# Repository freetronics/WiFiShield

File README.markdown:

Freetronics WiFi Shield

PCB fab stackup: 2-layer FR-4, 0.8mm thick. 0.8mm thickness is important to keep the waveguide impedence in the right ballpark.

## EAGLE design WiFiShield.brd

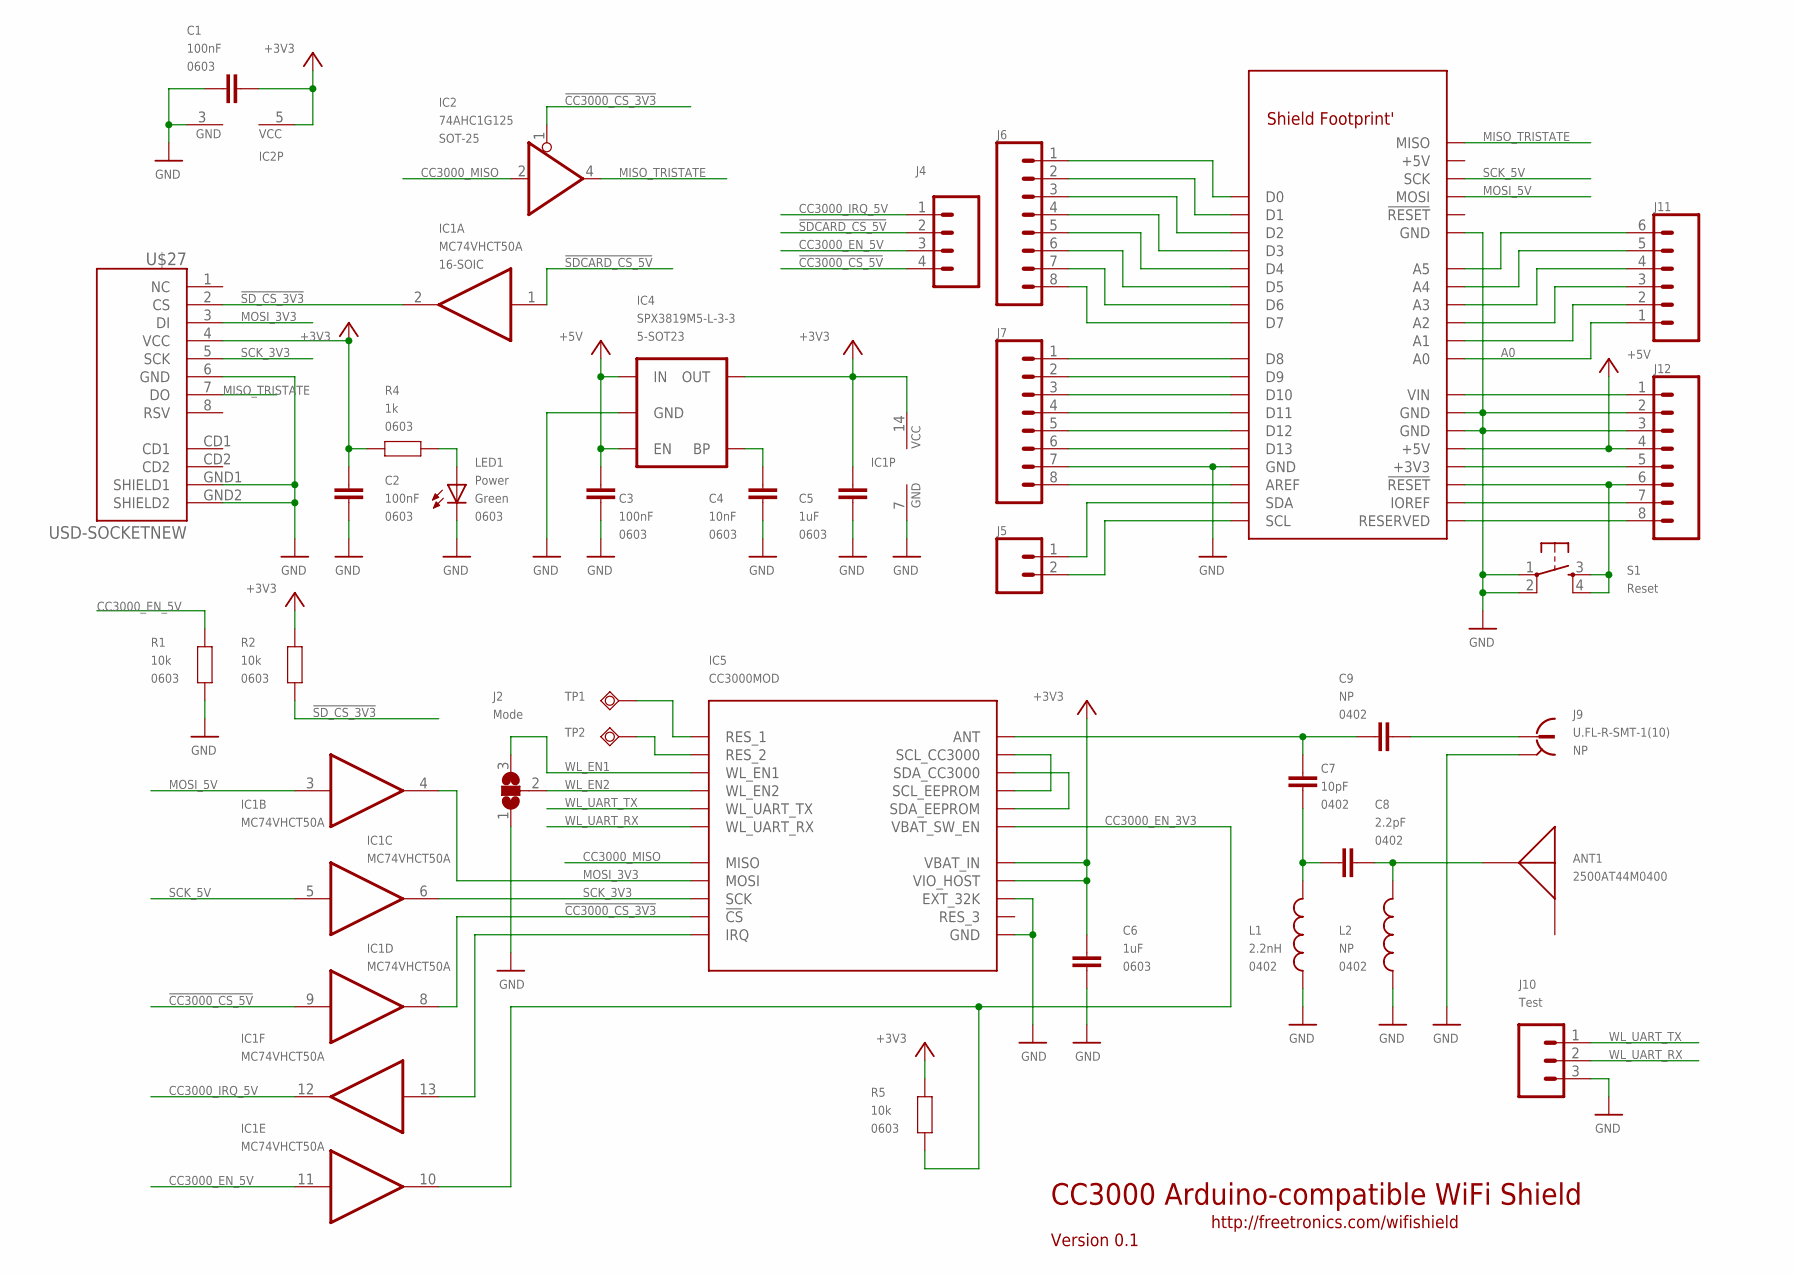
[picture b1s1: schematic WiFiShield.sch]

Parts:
ANT1: 2500AT44M0400
C1, C2, C3: 100nF; 0603
C4: 10nF; 0603
C5, C6: 1uF; 0603
C7: 10pF; C0402
C8: 2.2pF; C0402
C9: NP; C0402
IC1: MC74VHCT50A; SO14
IC2: 74AHC1G125; SOT23-5
IC4: SPX3819M5-L-3-3; SOT23-5
IC5: CC3000MOD; CC3000
J2: Mode; SJ_2
J4: M04PTH; 1X04
J5: M02PTH; 1X02
J6, J7, J12: M08STD; 1X08
J8: ARDUINO-SHIELD_R3; ARDUINO-SHIELD_R3_NOHOLES
J9: U.FL-R-SMT-1(10); UFL
J10: Test; 1X03
J11: M06SIP; 1X06
L1: 2.2nH; C0402
L2: NP; C0402
LED1: Power; LED-0603
R1, R2, R5: 10k; 0603
R4: 1k; 0603
S1: Reset; TACTILE_SWITCH_SMD
TP1: R1; TP06R
TP2: R2; TP06R
U$27: USD-SOCKETNEW; MICRO-SD-SOCKET-PP

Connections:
!CC3000_CS_3V3: IC1.8 (O), IC2.1 (OE), IC5.12 (!CS)
!CC3000_CS_5V: IC1.9 (I), J4.4
!SDCARD_CS_5V: IC1.1 (I), J4.2
!SD_CS_3V3: IC1.2 (O), R2.2, U$27.2 (CS)
+3V3: C1.2, C2.1, C5.1, C6.2, IC1.14 (VCC), IC2.5 (VCC), IC4.5 (OUT), IC5.19 (VBAT_IN), IC5.23 (VIO_HOST), R2.1, R4.2, R5.1, U$27.4 (VCC)
+5V: C3.2, IC4.1 (IN), IC4.3 (EN), J8.+5V, J12.4
A0: J8.A0, J11.1
CC3000_EN_3V3: IC1.10 (O), IC5.26 (VBAT_SW_EN), R5.2
CC3000_EN_5V: IC1.11 (I), J4.3, R1.1
CC3000_IRQ_5V: IC1.12 (O), J4.1
CC3000_MISO: IC2.2 (I), IC5.13 (MISO)
GND: C1.1, C2.2, C3.1, C4.1, C5.2, C6.1, IC1.7 (GND), IC2.3 (GND), IC4.2 (GND), IC5.1 (GND), IC5.9 (GND), IC5.10 (GND), IC5.11 (GND), IC5.16 (GND), IC5.18 (GND), IC5.20 (GND), IC5.21 (EXT_32K), IC5.22 (GND), IC5.25 (GND), IC5.31 (GND), IC5.32 (GND), IC5.33 (GND), IC5.34 (GND), IC5.36 (GND), IC5.37 (GND), IC5.38 (GND), IC5.39 (GND), IC5.40 (GND), IC5.41 (GND), IC5.42 (GND), IC5.43 (GND), IC5.44 (GND), IC5.45 (GND), IC5.46 (GND), J2.1, J7.7, J8.GND, J8.GND@0 (GND), J8.GND@1 (GND), J8.GND@2 (GND), J9.GND, J9.GND@1 (GND), J10.3, J12.2, J12.3, L1.2, L2.2, LED1.C, R1.2, S1.1, S1.2, U$27.6 (GND), U$27.GND1 (SHIELD1), U$27.GND2 (SHIELD2)
IOREF: J8.IOREF, J12.7
MISO_TRISTATE: IC2.4 (O), J8.MISO, U$27.7 (DO)
MOSI_3V3: IC1.4 (O), IC5.15 (MOSI), U$27.3 (DI)
MOSI_5V: IC1.3 (I), J8.MOSI
unnamed: IC5.27 (SDA_EEPROM), IC5.28 (SDA_CC3000)
unnamed: IC5.29 (SCL_EEPROM), IC5.30 (SCL_CC3000)
unnamed: LED1.A, R4.1
unnamed: C7.2, C9.2, IC5.35 (ANT)
unnamed: IC5.4 (RES_2), TP2.TP
unnamed: IC5.2 (RES_1), TP1.TP
unnamed: C9.1, J9.SIG
unnamed: IC1.13 (I), IC5.14 (IRQ)
unnamed: C4.2, IC4.4 (BP)
unnamed: J8.A1, J11.2
unnamed: J8.A2, J11.3
unnamed: J8.A3, J11.4
unnamed: J8.A4, J11.5
unnamed: J8.A5, J11.6
unnamed: J8.RESERVED, J12.8
unnamed: J8.VIN, J12.1
unnamed: J8.3V3 (+3V3), J12.5
unnamed: J8.!RESET, J12.6, S1.3, S1.4
unnamed: J6.1, J8.D0
unnamed: J6.2, J8.D1
unnamed: J6.3, J8.D2
unnamed: J6.4, J8.D3
unnamed: J6.5, J8.D4
unnamed: C7.1, C8.2, L1.1
unnamed: ANT1.P$1, C8.1, L2.1
unnamed: J6.6, J8.D5
unnamed: J6.7, J8.D6
unnamed: J6.8, J8.D7
unnamed: J5.1, J8.SDA
unnamed: J7.8, J8.AREF
unnamed: J7.6, J8.D13
unnamed: J7.5, J8.D12
unnamed: J5.2, J8.SCL
unnamed: J7.1, J8.D8
unnamed: J7.2, J8.D9
unnamed: J7.3, J8.D10
unnamed: J7.4, J8.D11
SCK_3V3: IC1.6 (O), IC5.17 (SCK), U$27.5 (SCK)
SCK_5V: IC1.5 (I), J8.SCK
WL_EN1: IC5.7 (WL_EN1), J2.3
WL_EN2: IC5.5 (WL_EN2), J2.2
WL_UART_RX: IC5.8 (WL_UART_RX), J10.2
WL_UART_TX: IC5.6 (WL_UART_TX), J10.1

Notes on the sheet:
CC3000 Arduino-compatible WiFi Shield
Version 0.1
http://freetronics.com/wifishield

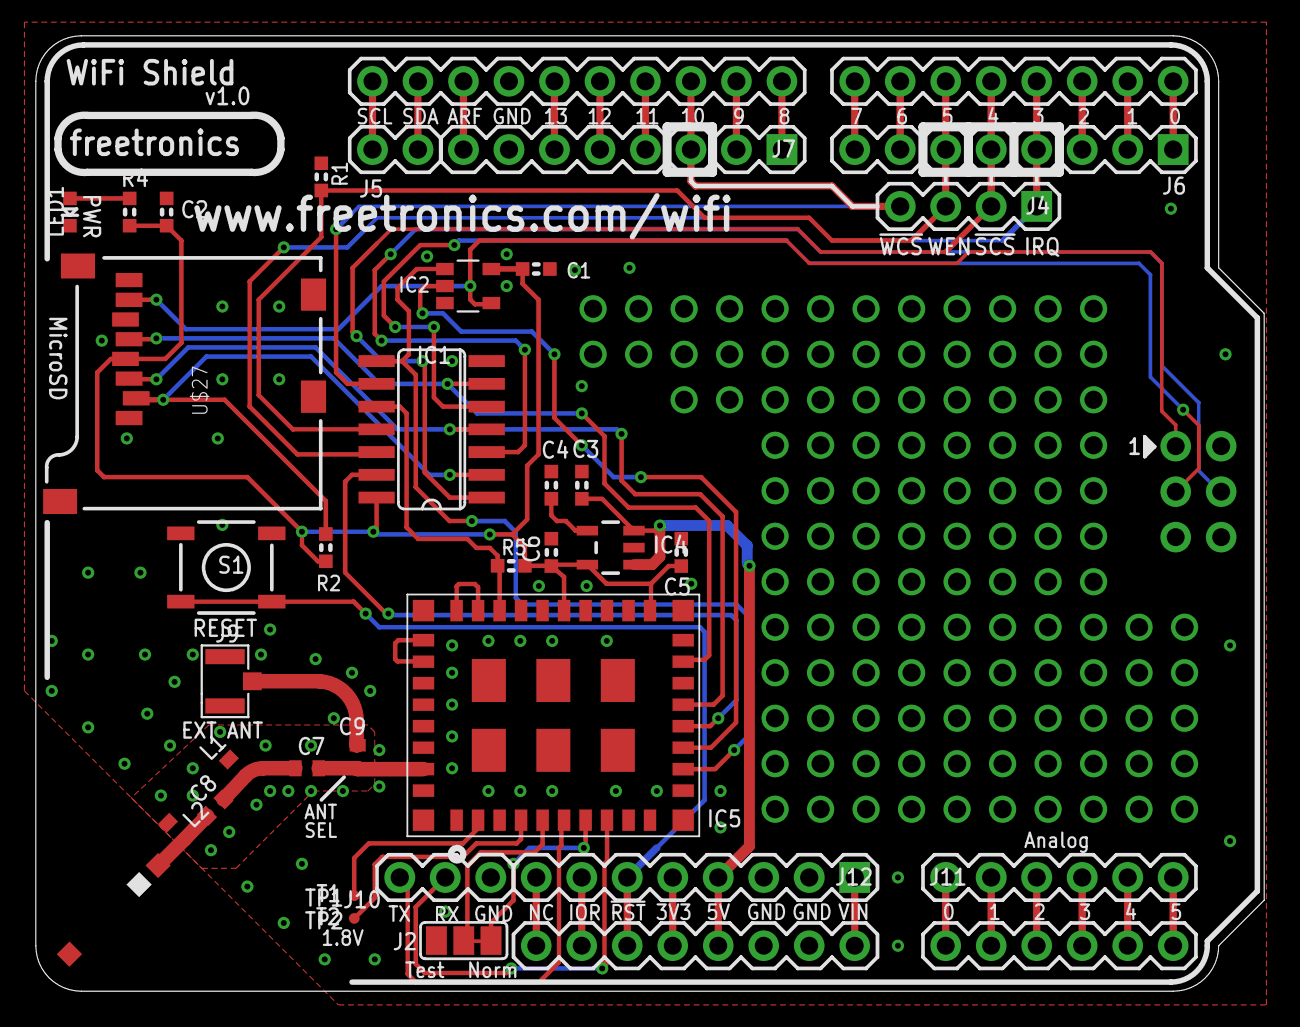
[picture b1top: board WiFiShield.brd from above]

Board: 2 copper layers, 68.6 x 53.3 mm, 35 parts (0 on the bottom side), 59 nets.

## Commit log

2013-10-12 added initial prototype design
2013-10-12 added preview image
2014-04-10 Added tristate buffer on MISO to fix CC3000 SPI bug, some minor tweaks, pull-ups added on nCS lines and CC3000 enable, silkscreen label tweaks.
2014-04-10 added placement overlay
2014-04-10 regenerated images and gerbers
2014-07-08 Swap adafruit microsd slot for (very similar) freetronics library footprint, remove sometimes-problematic CD line
2014-07-08 Swap 4050 buffer for MC74VHCT50A (stocked part, used on FTOLED.)
2014-07-08 Add gitignore
2014-07-09 Fixups for MC74VHCT
2014-07-09 Remove temp sensor
2014-07-09 Add silkscreen border
2014-07-09 Update breakout/silkscreen to match 7f99dbe3f
2014-07-11 Additional rear silkscreen
2014-07-24 Switch to chip antenna, final pre-prototype design review
2014-07-24 Minor cleanup
2014-08-11 Replace accidentally deleted wire
2014-08-11 Update schematic PDF
2014-09-10 Juggle antenna routing a bit
2014-09-10 Swap R1 to be pulldown on enable
2014-09-10 Increase pad restring, move some traces around
2014-09-10 Swap SPX3819 LDO for AP2112K-3.3

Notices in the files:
WiFiShield.brd:
(C) 2014 Freetronics Pty Ltd
Licensed under TAPR
Open Hardware License
